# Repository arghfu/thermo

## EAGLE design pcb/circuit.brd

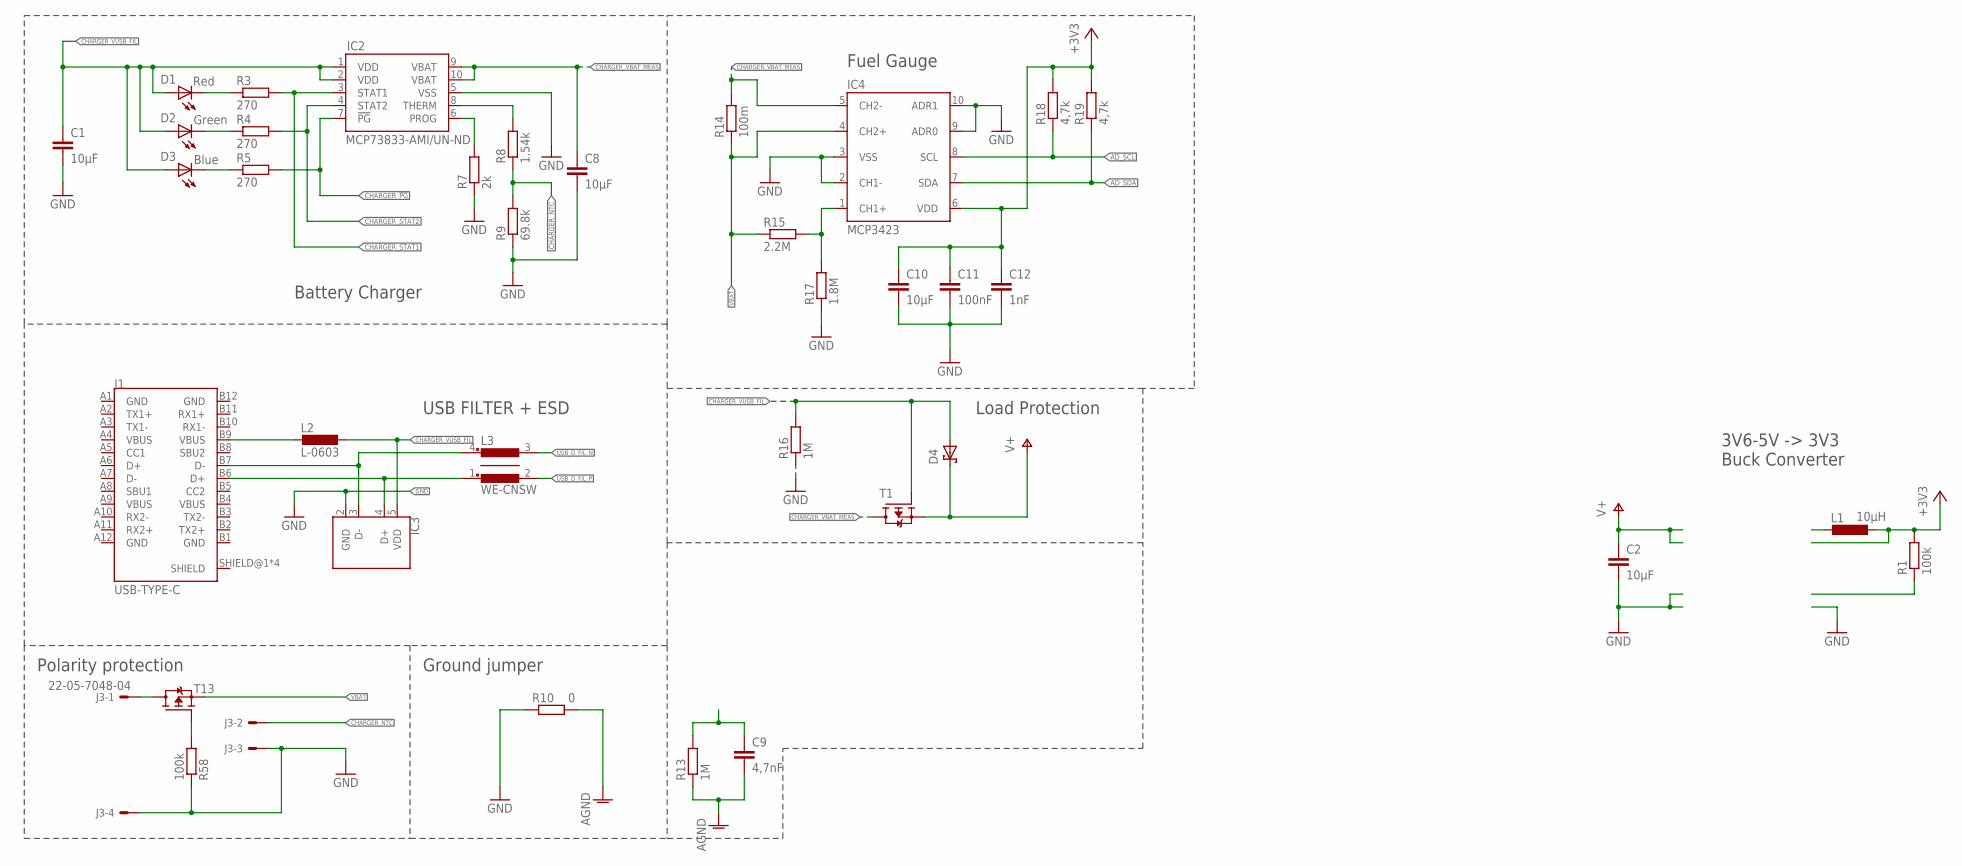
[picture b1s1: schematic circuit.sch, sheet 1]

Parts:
C1, C2, C8, C10: 10µF; C0805
C9: 4,7nF; C0603
C11: 100nF; C0603
C12: 1nF; C0603
D1: Red; LED_2012
D2: Green; LED_2012
D3: Blue; LED_2012
D4: BAT60AE6327HTSA1; SOD323
IC2: MCP73833-AMI/UN-ND; MSOP10
IC3: WE-TVS; SOT23-5L
IC4: MCP3423; MSOP10
J1: USB-TYPE-C; USB-105450-0101
J3: 22-05-7048-04; 7395-04
L1: 10µH; L-1210
L2: L-0603; L0603
L3: WE-CNSW
R1, R58: 100k; R0603
R3, R4, R5: 270; R0603
R7: 2k; R0603
R8: 1.54k; R0603
R9: 69.8k; R0603
R10: 0; R0603
R13, R16: 1M; R0603
R14: 100m; R5025
R15: 2.2M; R0603
R17: 1.8M; R0603
R18, R19: 4,7k; R0603
T1, T13: PMOS; SOT23

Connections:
+3V3: C10.1, C11.1, C12.1, IC4.6 (VDD), L1.1, R1.2, R18.2, R19.2; also elsewhere on the board
AD_CH2+: IC4.1 (CH1+), R15.2, R17.2
AD_SCL: IC4.8 (SCL), R18.1; also elsewhere on the board
AD_SDA: IC4.7 (SDA), R19.1; also elsewhere on the board
AGND: C9.2, R10.2, R13.1; also elsewhere on the board
BUCK_LX: L1.2
CHARGER_!PG!: IC2.7 (!PG), R5.2; also elsewhere on the board
CHARGER_!PG!_LED: D3.1 (C), R5.1
CHARGER_NTC: J3.2, R8.1, R9.2
CHARGER_PROG: IC2.6 (PROG), R7.2
CHARGER_STAT1: IC2.3 (STAT1), R3.2; also elsewhere on the board
CHARGER_STAT1_LED: D1.1 (C), R3.1
CHARGER_STAT2: IC2.4 (STAT2), R4.2; also elsewhere on the board
CHARGER_STAT2_LED: D2.1 (C), R4.1
CHARGER_THERM: IC2.8 (THERM), R8.2
CHARGER_VBAT_MEAS: C8.1, IC2.9 (VBAT), IC2.10 (VBAT), IC4.5 (CH2-), R14.2, T1.3 (D)
CHARGER_VUSB_FIL: C1.1, D1.2 (A), D2.2 (A), D3.2 (A), D4.2 (A), IC2.1 (VDD), IC2.2 (VDD), IC3.5 (VDD), L2.1, R16.2, T1.1 (G); also elsewhere on the board
GND: C1.2, C2.2, C8.2, C10.2, C11.2, C12.2, IC2.5 (VSS), IC3.2 (GND), IC4.2 (CH1-), IC4.3 (VSS), IC4.9 (ADR0), IC4.10 (ADR1), J3.3, J3.4, R7.1, R9.1, R10.1, R16.1, R17.1, R58.1; also elsewhere on the board
unnamed: J1.B9 (VBUS), L2.2
USB_D_FIL_N: L3.3; also elsewhere on the board
USB_D_FIL_P: L3.2; also elsewhere on the board
USB_D_N: IC3.3 (D-), J1.A7 (D-), J1.B7 (D-), L3.4
USB_D_P: IC3.4 (D+), J1.A6 (D+), J1.B6 (D+), L3.1
USB_SHIELD: C9.1, R13.2
V+: C2.1, D4.1 (C), T1.2 (S)
VAT_EN: R58.2, T13.1 (G)
VBAT: IC4.4 (CH2+), R14.1, R15.1, T13.2 (S)
VBAT_UNPROT: J3.1, T13.3 (D)

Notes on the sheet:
3V6-5V -> 3V3 Buck Converter
Fuel Gauge
Battery Charger
Load Protection
USB FILTER + ESD
Polarity protection
Ground jumper

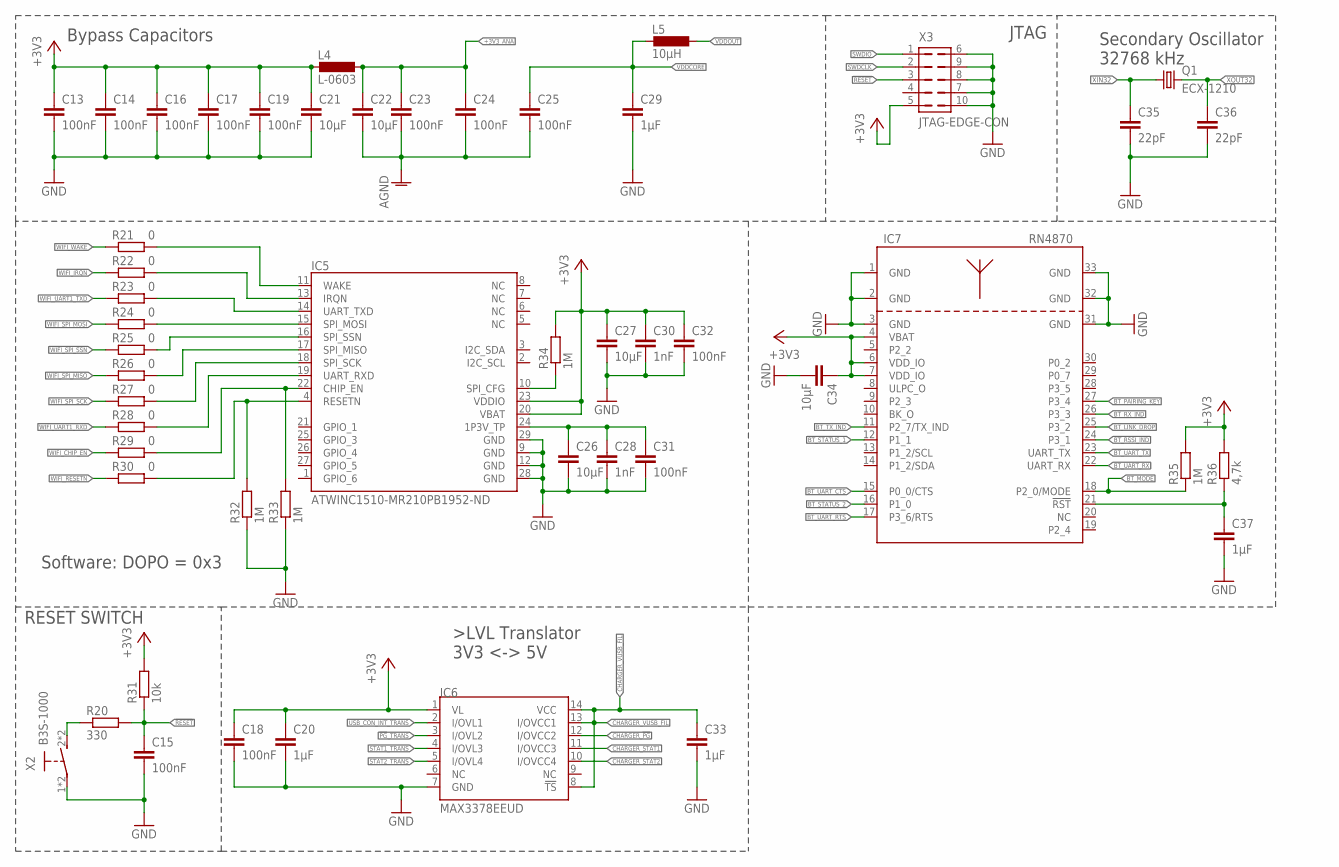
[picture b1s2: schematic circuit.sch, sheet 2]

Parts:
C13, C14, C15, C16, C17, C18, C19, C23, C24, C25, C31, C32: 100nF; C0603
C20, C29, C33, C37: 1µF; C0603
C21, C22, C26, C27, C34: 10µF; C0805
C28, C30: 1nF; C0603
C35, C36: 22pF; C0603
IC5: ATWINC1510-MR210PB1952-ND; ATWINC15X0-MODULE
IC6: MAX3378EEUD; TSSOP14
IC7: RN4870; RN4870-MODULE
L4: L-0603; L0603
L5: 10µH; L-1210
Q1: ECX-1210
R20: 330; R0603
R21, R22, R23, R24, R25, R26, R27, R28, R29, R30: 0; R0603
R31: 10k; R0603
R32, R33, R34, R35: 1M; R0603
R36: 4,7k; R0603
X2: B3S-1000; B3S
X3: JTAG-EDGE-CON; DEBUG-CON

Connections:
!PG!_TRANS: IC6.3 (I/OVL2); also elsewhere on the board
!RESET!: C15.1, R20.2, R31.1, X3.3; also elsewhere on the board
!RESET!_B: R20.1, X2.2 (S), X2.4 (S)
+3V3: C13.1, C14.1, C16.1, C17.1, C18.1, C19.1, C20.1, C21.1, C27.1, C30.1, C32.1, C34.1, IC5.20 (VBAT), IC5.23 (VDDIO), IC6.1 (VL), IC7.4 (VBAT), IC7.6 (VDD_IO), IC7.7 (VDD_IO), L4.2, R31.2, R34.2, R35.2, R36.2, X3.5; also elsewhere on the board
+3V3_ANA: C22.1, C23.1, C24.1, L4.1; also elsewhere on the board
AGND: C22.2, C23.2, C24.2, C25.2; also elsewhere on the board
BT_!RESET!: C37.1, IC7.21 (!RST!), R36.1
BT_LINK_DROP: IC7.25 (P3_2); also elsewhere on the board
BT_MODE: IC7.18 (P2_0/MODE), R35.1; also elsewhere on the board
BT_PAIRING_KEY: IC7.27 (P3_4); also elsewhere on the board
BT_RSSI_IND: IC7.24 (P3_1); also elsewhere on the board
BT_RX_IND: IC7.26 (P3_3); also elsewhere on the board
BT_STATUS_1: IC7.12 (P1_1); also elsewhere on the board
BT_STATUS_2: IC7.16 (P1_0); also elsewhere on the board
BT_TX_IND: IC7.11 (P2_7/TX_IND); also elsewhere on the board
BT_UART_CTS: IC7.15 (P0_0/CTS); also elsewhere on the board
BT_UART_RTS: IC7.17 (P3_6/RTS); also elsewhere on the board
BT_UART_RX: IC7.22 (UART_RX); also elsewhere on the board
BT_UART_TX: IC7.23 (UART_TX); also elsewhere on the board
CHARGER_!PG!: IC6.12 (I/OVCC2); also elsewhere on the board
CHARGER_STAT1: IC6.11 (I/OVCC3); also elsewhere on the board
CHARGER_STAT2: IC6.10 (I/OVCC4); also elsewhere on the board
CHARGER_VUSB_FIL: C33.1, IC6.8 (!TS!), IC6.13 (I/OVCC1), IC6.14 (VCC); also elsewhere on the board
GND: C13.2, C14.2, C15.2, C16.2, C17.2, C18.2, C19.2, C20.2, C21.2, C26.2, C27.2, C28.2, C29.2, C30.2, C31.2, C32.2, C33.2, C34.2, C35.2, C36.2, C37.2, IC5.9 (GND), IC5.12 (GND), IC5.28 (GND), IC5.29 (GND), IC6.7 (GND), IC7.1 (GND), IC7.2 (GND), IC7.3 (GND), IC7.31 (GND), IC7.32 (GND), IC7.33 (GND), R32.1, R33.1, X2.1, X2.3, X3.6, X3.7, X3.8, X3.9, X3.10; also elsewhere on the board
STAT1_TRANS: IC6.4 (I/OVL3); also elsewhere on the board
STAT2_TRANS: IC6.5 (I/OVL4); also elsewhere on the board
SWDCLK: X3.2; also elsewhere on the board
SWDIO: X3.1; also elsewhere on the board
USB_CON_INT_TRANS: IC6.2 (I/OVL1); also elsewhere on the board
VDDCORE: C25.1, C29.1, L5.2; also elsewhere on the board
VDDOUT: L5.1; also elsewhere on the board
WIFI_1P3V_TP: C26.1, C28.1, C31.1, IC5.24 (1P3V_TP)
WIFI_CHIP_EN: R29.1; also elsewhere on the board
WIFI_CHIP_EN_D: IC5.22 (CHIP_EN), R29.2, R33.2
WIFI_IRQN: R22.1; also elsewhere on the board
WIFI_IRQN_D: IC5.13 (IRQN), R22.2
WIFI_MOSI_D: IC5.15 (SPI_MOSI), R24.2
WIFI_RESETN: R30.1; also elsewhere on the board
WIFI_RESETN_D: IC5.4 (RESETN), R30.2, R32.2
WIFI_SPI_CFG: IC5.10 (SPI_CFG), R34.1
WIFI_SPI_MISO: R26.1; also elsewhere on the board
WIFI_SPI_MISO_D: IC5.17 (SPI_MISO), R26.2
WIFI_SPI_MOSI: R24.1; also elsewhere on the board
WIFI_SPI_SCK: R27.1; also elsewhere on the board
WIFI_SPI_SCK_D: IC5.18 (SPI_SCK), R27.2
WIFI_SPI_SSN: R25.1; also elsewhere on the board
WIFI_SPI_SSN_D: IC5.16 (SPI_SSN), R25.2
WIFI_UART1_RXD: R28.1; also elsewhere on the board
WIFI_UART1_RXD_D: IC5.19 (UART_RXD), R28.2
WIFI_UART1_TXD: R23.1; also elsewhere on the board
WIFI_UART_TXD_D: IC5.14 (UART_TXD), R23.2
WIFI_WAKE: R21.1; also elsewhere on the board
WIFI_WAKE_D: IC5.11 (WAKE), R21.2
XIN32: C35.1, Q1.1; also elsewhere on the board
XOUT32: C36.1, Q1.2; also elsewhere on the board

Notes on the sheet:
Bypass Capacitors
Secondary Oscillator 32768 kHz
RESET SWITCH
JTAG
Software: DOPO = 0x3

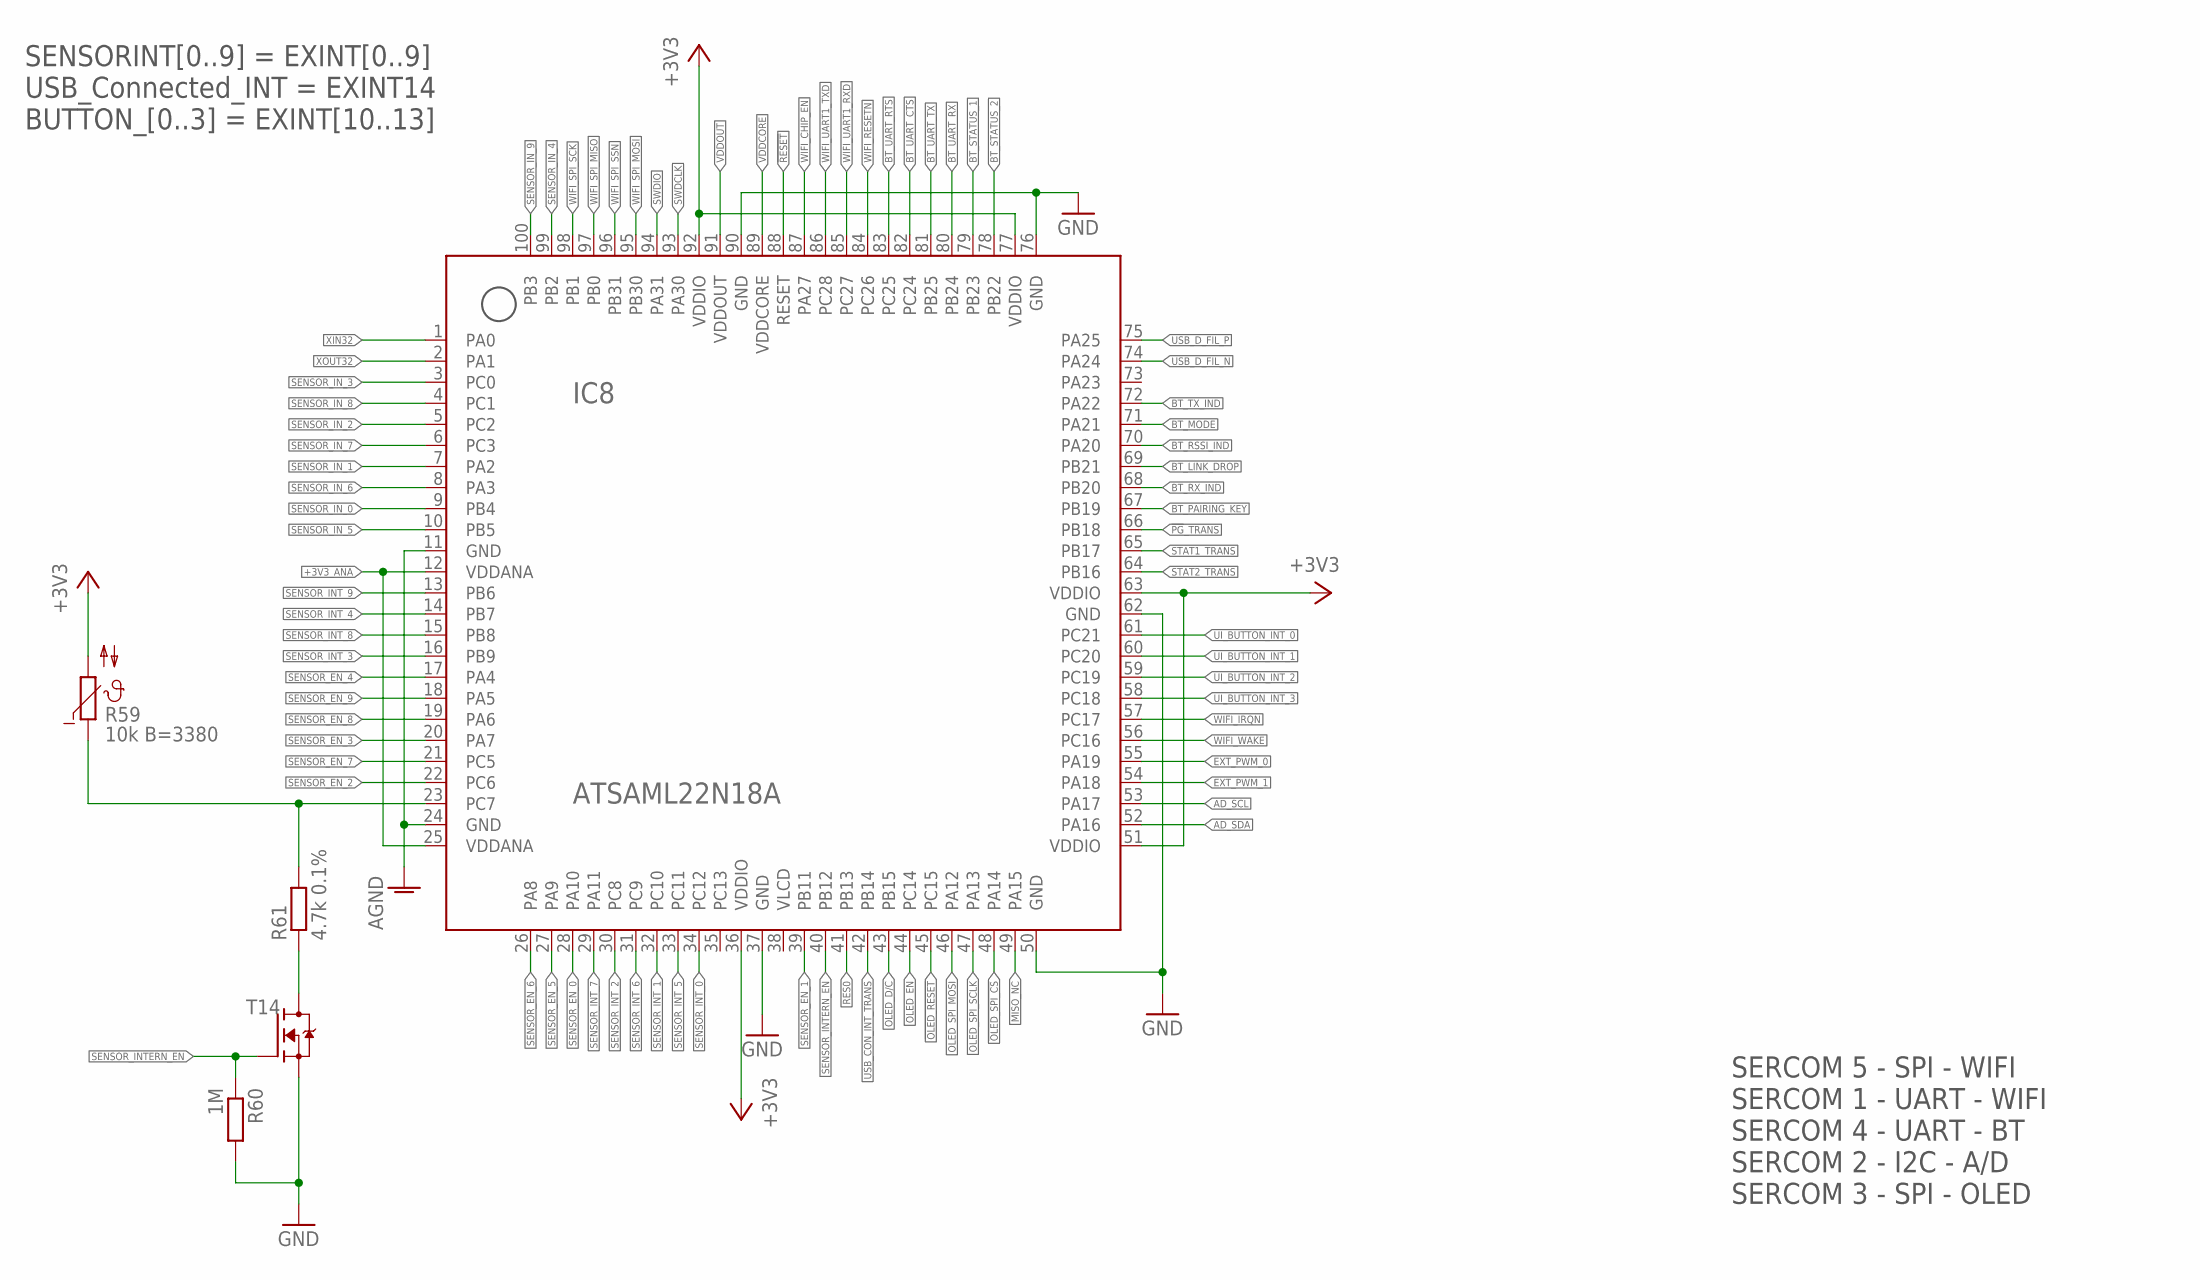
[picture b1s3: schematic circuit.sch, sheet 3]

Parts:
IC8: ATSAML22N18A; TQFP100
R59: 10k B=3380; R0603
R60: 1M; R0603
R61: 4.7k 0.1%; R0603
T14: NMOSSOT323; SOT-323

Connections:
!OLED_RESET: IC8.45 (PC15); also elsewhere on the board
!OLED_SPI_CS: IC8.48 (PA14); also elsewhere on the board
!PG!_TRANS: IC8.66 (PB18); also elsewhere on the board
!RESET!: IC8.88 (RESET); also elsewhere on the board
+3V3: IC8.36 (VDDIO), IC8.51 (VDDIO), IC8.63 (VDDIO), IC8.77 (VDDIO), IC8.92 (VDDIO), R59.2; also elsewhere on the board
+3V3_ANA: IC8.12 (VDDANA), IC8.25 (VDDANA); also elsewhere on the board
AD_SCL: IC8.53 (PA17); also elsewhere on the board
AD_SDA: IC8.52 (PA16); also elsewhere on the board
AGND: IC8.11 (GND), IC8.24 (GND); also elsewhere on the board
BT_LINK_DROP: IC8.69 (PB21); also elsewhere on the board
BT_MODE: IC8.71 (PA21); also elsewhere on the board
BT_PAIRING_KEY: IC8.67 (PB19); also elsewhere on the board
BT_RSSI_IND: IC8.70 (PA20); also elsewhere on the board
BT_RX_IND: IC8.68 (PB20); also elsewhere on the board
BT_STATUS_1: IC8.79 (PB23); also elsewhere on the board
BT_STATUS_2: IC8.78 (PB22); also elsewhere on the board
BT_TX_IND: IC8.72 (PA22); also elsewhere on the board
BT_UART_CTS: IC8.82 (PC24); also elsewhere on the board
BT_UART_RTS: IC8.83 (PC25); also elsewhere on the board
BT_UART_RX: IC8.80 (PB24); also elsewhere on the board
BT_UART_TX: IC8.81 (PB25); also elsewhere on the board
EXT_PWM_0: IC8.55 (PA19); also elsewhere on the board
EXT_PWM_1: IC8.54 (PA18); also elsewhere on the board
GND: IC8.37 (GND), IC8.50 (GND), IC8.62 (GND), IC8.76 (GND), IC8.90 (GND), R60.2, T14.2 (S); also elsewhere on the board
MISO_NC: IC8.49 (PA15)
OLED_D/C: IC8.43 (PB15); also elsewhere on the board
OLED_EN: IC8.44 (PC14); also elsewhere on the board
OLED_SPI_MOSI: IC8.46 (PA12); also elsewhere on the board
OLED_SPI_SCLK: IC8.47 (PA13); also elsewhere on the board
RES0: IC8.41 (PB13); also elsewhere on the board
SENSOR_EN_0: IC8.28 (PA10); also elsewhere on the board
SENSOR_EN_1: IC8.39 (PB11); also elsewhere on the board
SENSOR_EN_2: IC8.22 (PC6); also elsewhere on the board
SENSOR_EN_3: IC8.20 (PA7); also elsewhere on the board
SENSOR_EN_4: IC8.17 (PA4); also elsewhere on the board
SENSOR_EN_5: IC8.27 (PA9); also elsewhere on the board
SENSOR_EN_6: IC8.26 (PA8); also elsewhere on the board
SENSOR_EN_7: IC8.21 (PC5); also elsewhere on the board
SENSOR_EN_8: IC8.19 (PA6); also elsewhere on the board
SENSOR_EN_9: IC8.18 (PA5); also elsewhere on the board
SENSOR_INTERN_DRAIN: R61.1, T14.3 (D)
SENSOR_INTERN_EN: IC8.40 (PB12), R60.1, T14.1 (G); also elsewhere on the board
SENSOR_INTERN_IN: IC8.23 (PC7), R59.1, R61.2
SENSOR_INT_0: IC8.34 (PC12); also elsewhere on the board
SENSOR_INT_1: IC8.32 (PC10); also elsewhere on the board
SENSOR_INT_2: IC8.30 (PC8); also elsewhere on the board
SENSOR_INT_3: IC8.16 (PB9); also elsewhere on the board
SENSOR_INT_4: IC8.14 (PB7); also elsewhere on the board
SENSOR_INT_5: IC8.33 (PC11); also elsewhere on the board
SENSOR_INT_6: IC8.31 (PC9); also elsewhere on the board
SENSOR_INT_7: IC8.29 (PA11); also elsewhere on the board
SENSOR_INT_8: IC8.15 (PB8); also elsewhere on the board
SENSOR_INT_9: IC8.13 (PB6); also elsewhere on the board
SENSOR_IN_0: IC8.9 (PB4); also elsewhere on the board
SENSOR_IN_1: IC8.7 (PA2); also elsewhere on the board
SENSOR_IN_2: IC8.5 (PC2); also elsewhere on the board
SENSOR_IN_3: IC8.3 (PC0); also elsewhere on the board
SENSOR_IN_4: IC8.99 (PB2); also elsewhere on the board
SENSOR_IN_5: IC8.10 (PB5); also elsewhere on the board
SENSOR_IN_6: IC8.8 (PA3); also elsewhere on the board
SENSOR_IN_7: IC8.6 (PC3); also elsewhere on the board
SENSOR_IN_8: IC8.4 (PC1); also elsewhere on the board
SENSOR_IN_9: IC8.100 (PB3); also elsewhere on the board
STAT1_TRANS: IC8.65 (PB17); also elsewhere on the board
STAT2_TRANS: IC8.64 (PB16); also elsewhere on the board
SWDCLK: IC8.93 (PA30); also elsewhere on the board
SWDIO: IC8.94 (PA31); also elsewhere on the board
UI_BUTTON_INT_0: IC8.61 (PC21); also elsewhere on the board
UI_BUTTON_INT_1: IC8.60 (PC20); also elsewhere on the board
UI_BUTTON_INT_2: IC8.59 (PC19); also elsewhere on the board
UI_BUTTON_INT_3: IC8.58 (PC18); also elsewhere on the board
USB_CON_INT_TRANS: IC8.42 (PB14); also elsewhere on the board
USB_D_FIL_N: IC8.74 (PA24); also elsewhere on the board
USB_D_FIL_P: IC8.75 (PA25); also elsewhere on the board
VDDCORE: IC8.89 (VDDCORE); also elsewhere on the board
VDDOUT: IC8.91 (VDDOUT); also elsewhere on the board
WIFI_CHIP_EN: IC8.87 (PA27); also elsewhere on the board
WIFI_IRQN: IC8.57 (PC17); also elsewhere on the board
WIFI_RESETN: IC8.84 (PC26); also elsewhere on the board
WIFI_SPI_MISO: IC8.97 (PB0); also elsewhere on the board
WIFI_SPI_MOSI: IC8.95 (PB30); also elsewhere on the board
WIFI_SPI_SCK: IC8.98 (PB1); also elsewhere on the board
WIFI_SPI_SSN: IC8.96 (PB31); also elsewhere on the board
WIFI_UART1_RXD: IC8.85 (PC27); also elsewhere on the board
WIFI_UART1_TXD: IC8.86 (PC28); also elsewhere on the board
WIFI_WAKE: IC8.56 (PC16); also elsewhere on the board
XIN32: IC8.1 (PA0); also elsewhere on the board
XOUT32: IC8.2 (PA1); also elsewhere on the board

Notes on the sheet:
SERCOM 5 - SPI - WIFI SERCOM 1 - UART - WIFI SERCOM 4 - UART - BT SERCOM 2 - I2C - A/D SERCOM 3 - SPI - OLED
SENSORINT[0..9] = EXINT[0..9] USB_Connected_INT = EXINT14 BUTTON_[0..3] = EXINT[10..13]

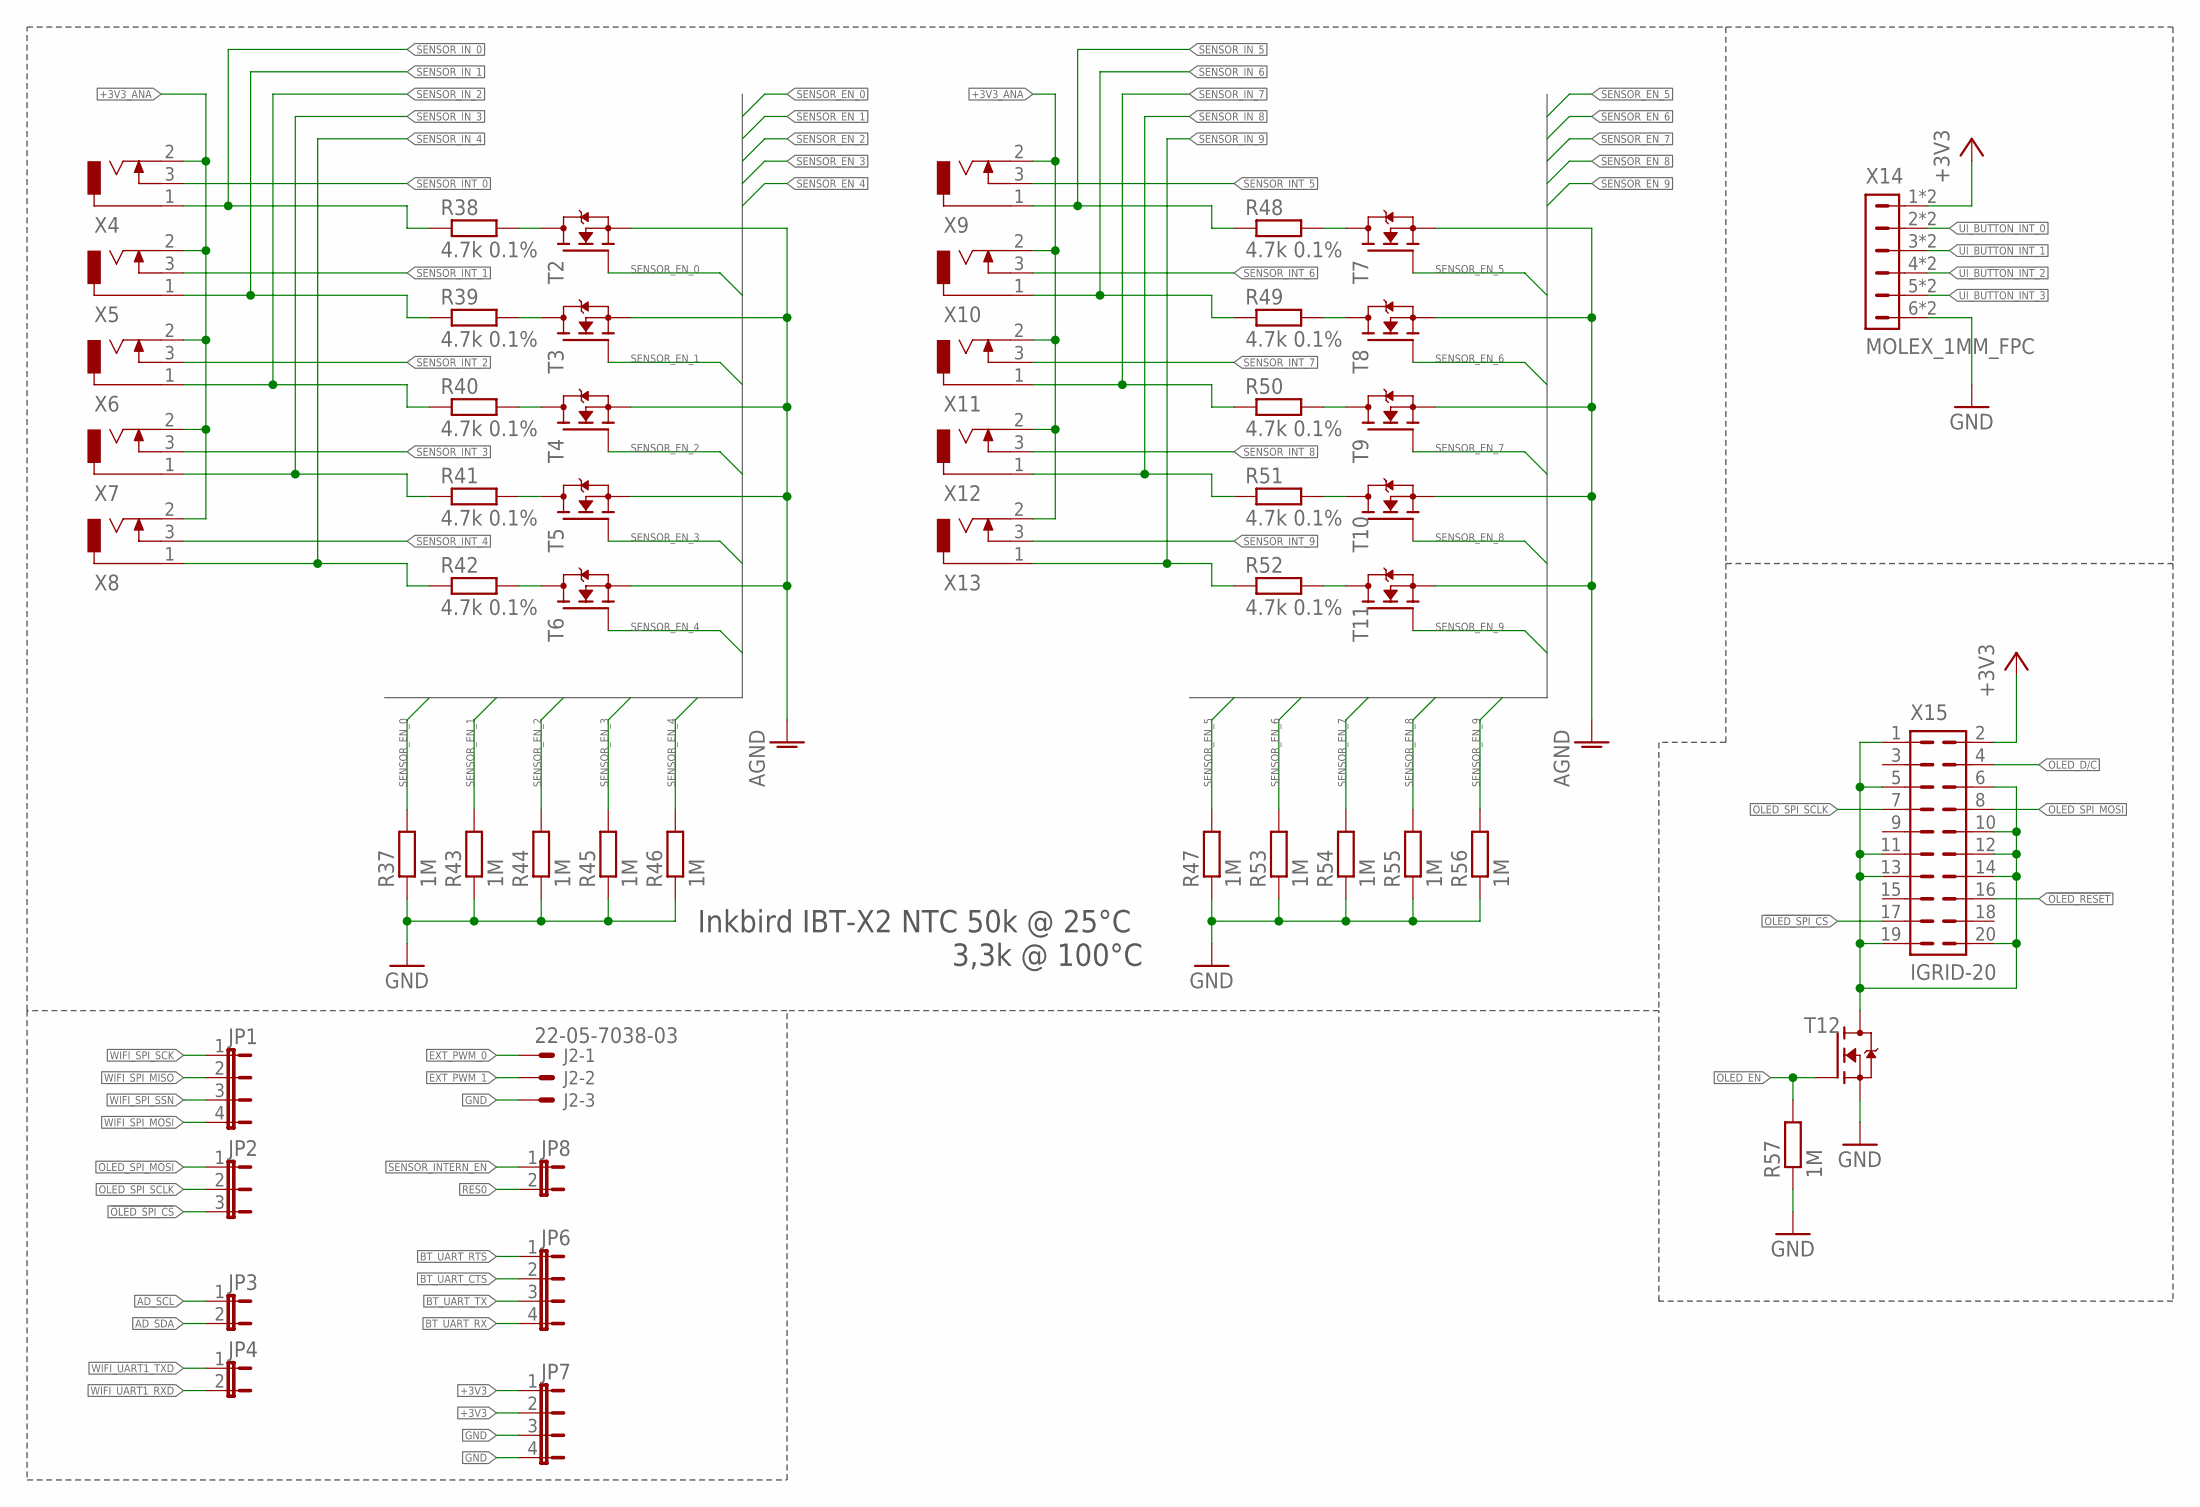
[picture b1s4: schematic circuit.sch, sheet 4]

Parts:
J2: 22-05-7038-03; 7395-03
JP1, JP6, JP7: JP4
JP2: JP3
JP3, JP4, JP8: JP2
R37, R43, R44, R45, R46, R47, R53, R54, R55, R56, R57: 1M; R0603
R38, R39, R40, R41, R42, R48, R49, R50, R51, R52: 4.7k 0.1%; R0603
T2, T3, T4, T5, T6, T7, T8, T9, T10, T11, T12: NMOSSOT323; SOT-323
X4, X5, X6, X7, X8: 2.5MM-AUDIO-JACK-MONODRILL; 2.5MM-AUDIO-JACK-MONO
X9, X10, X11, X12, X13: 2.5MM-AUDIO-JACK-MONONO_DRILL; 2.5MM-AUDIO-JACK-MONO-2
X14: MOLEX_1MM_FPC; 1MM_FPC_ZIF
X15: IGRID-20; I-GRID-20

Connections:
!OLED_RESET: X15.16; also elsewhere on the board
!OLED_SPI_CS: JP2.3, X15.17; also elsewhere on the board
+3V3: JP7.1, JP7.2, X14.1, X14.7 (1), X15.2; also elsewhere on the board
+3V3_ANA: X4.2, X5.2, X6.2, X7.2, X8.2, X9.2, X10.2, X11.2, X12.2, X13.2; also elsewhere on the board
AD_SCL: JP3.1; also elsewhere on the board
AD_SDA: JP3.2; also elsewhere on the board
AGND: T2.2 (S), T3.2 (S), T4.2 (S), T5.2 (S), T6.2 (S), T7.2 (S), T8.2 (S), T9.2 (S), T10.2 (S), T11.2 (S); also elsewhere on the board
BT_UART_CTS: JP6.2; also elsewhere on the board
BT_UART_RTS: JP6.1; also elsewhere on the board
BT_UART_RX: JP6.4; also elsewhere on the board
BT_UART_TX: JP6.3; also elsewhere on the board
EXT_PWM_0: J2.1; also elsewhere on the board
EXT_PWM_1: J2.2; also elsewhere on the board
GND: J2.3, JP7.3, JP7.4, R37.1, R43.1, R44.1, R45.1, R46.1, R47.1, R53.1, R54.1, R55.1, R56.1, R57.1, T12.2 (S), X14.6, X14.12 (6); also elsewhere on the board
OLED_D/C: X15.4; also elsewhere on the board
OLED_EN: R57.2, T12.1 (G); also elsewhere on the board
OLED_EN_DRAIN: T12.3 (D), X15.1, X15.5, X15.6, X15.10, X15.11, X15.12, X15.13, X15.14, X15.19, X15.20
OLED_SPI_MOSI: JP2.1, X15.8; also elsewhere on the board
OLED_SPI_SCLK: JP2.2, X15.7; also elsewhere on the board
RES0: JP8.2; also elsewhere on the board
SENSOR_EN_0: R37.2, T2.1 (G); also elsewhere on the board
SENSOR_EN_1: R43.2, T3.1 (G); also elsewhere on the board
SENSOR_EN_2: R44.2, T4.1 (G); also elsewhere on the board
SENSOR_EN_3: R45.2, T5.1 (G); also elsewhere on the board
SENSOR_EN_4: R46.2, T6.1 (G); also elsewhere on the board
SENSOR_EN_5: R47.2, T7.1 (G); also elsewhere on the board
SENSOR_EN_6: R53.2, T8.1 (G); also elsewhere on the board
SENSOR_EN_7: R54.2, T9.1 (G); also elsewhere on the board
SENSOR_EN_8: R55.2, T10.1 (G); also elsewhere on the board
SENSOR_EN_9: R56.2, T11.1 (G); also elsewhere on the board
SENSOR_INTERN_EN: JP8.1; also elsewhere on the board
SENSOR_INT_0: X4.3; also elsewhere on the board
SENSOR_INT_1: X5.3; also elsewhere on the board
SENSOR_INT_2: X6.3; also elsewhere on the board
SENSOR_INT_3: X7.3; also elsewhere on the board
SENSOR_INT_4: X8.3; also elsewhere on the board
SENSOR_INT_5: X9.3; also elsewhere on the board
SENSOR_INT_6: X10.3; also elsewhere on the board
SENSOR_INT_7: X11.3; also elsewhere on the board
SENSOR_INT_8: X12.3; also elsewhere on the board
SENSOR_INT_9: X13.3; also elsewhere on the board
SENSOR_IN_0: R38.1, X4.1; also elsewhere on the board
SENSOR_IN_0_DRAIN: R38.2, T2.3 (D)
SENSOR_IN_1: R39.1, X5.1; also elsewhere on the board
SENSOR_IN_1_DRAIN: R39.2, T3.3 (D)
SENSOR_IN_2: R40.1, X6.1; also elsewhere on the board
SENSOR_IN_2_DRAIN: R40.2, T4.3 (D)
SENSOR_IN_3: R41.1, X7.1; also elsewhere on the board
SENSOR_IN_3_DRAIN: R41.2, T5.3 (D)
SENSOR_IN_4: R42.1, X8.1; also elsewhere on the board
SENSOR_IN_4_DRAIN: R42.2, T6.3 (D)
SENSOR_IN_5: R48.1, X9.1; also elsewhere on the board
SENSOR_IN_5_DRAIN: R48.2, T7.3 (D)
SENSOR_IN_6: R49.1, X10.1; also elsewhere on the board
SENSOR_IN_6_DRAIN: R49.2, T8.3 (D)
SENSOR_IN_7: R50.1, X11.1; also elsewhere on the board
SENSOR_IN_7_DRAIN: R50.2, T9.3 (D)
SENSOR_IN_8: R51.1, X12.1; also elsewhere on the board
SENSOR_IN_8_DRAIN: R51.2, T10.3 (D)
SENSOR_IN_9: R52.1, X13.1; also elsewhere on the board
SENSOR_IN_9_DRAIN: R52.2, T11.3 (D)
UI_BUTTON_INT_0: X14.2, X14.8 (2); also elsewhere on the board
UI_BUTTON_INT_1: X14.3, X14.9 (3); also elsewhere on the board
UI_BUTTON_INT_2: X14.4, X14.10 (4); also elsewhere on the board
UI_BUTTON_INT_3: X14.5, X14.11 (5); also elsewhere on the board
WIFI_SPI_MISO: JP1.2; also elsewhere on the board
WIFI_SPI_MOSI: JP1.4; also elsewhere on the board
WIFI_SPI_SCK: JP1.1; also elsewhere on the board
WIFI_SPI_SSN: JP1.3; also elsewhere on the board
WIFI_UART1_RXD: JP4.2; also elsewhere on the board
WIFI_UART1_TXD: JP4.1; also elsewhere on the board

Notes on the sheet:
Inkbird IBT-X2 NTC 50k @ 25°C 3,3k @ 100°C

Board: 2 copper layers, 144 parts (0 on the bottom side), 132 nets, no tracks yet.

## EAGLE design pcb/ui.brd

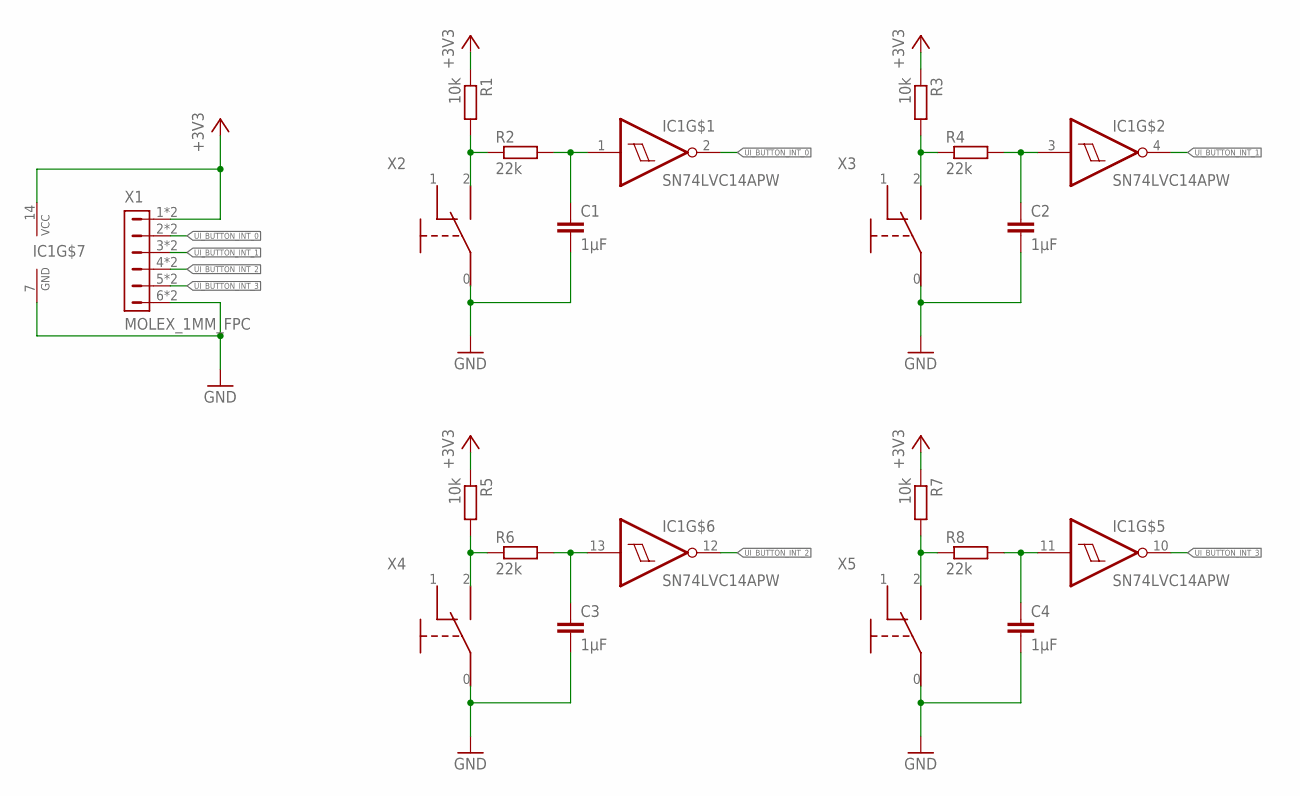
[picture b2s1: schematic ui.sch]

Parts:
C1, C2, C3, C4: 1µF; C0805
IC1: SN74LVC14APW; TSSOP14
R1, R3, R5, R7: 10k; R0805
R2, R4, R6, R8: 22k; R0805
X1: MOLEX_1MM_FPC; 1MM_FPC_ZIF
X2, X3, X4, X5: PVA2OAH11.7NV2; BUTTON-2

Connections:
+3V3: IC1.14 (VCC), R1.1, R3.1, R5.1, R7.1, X1.1, X1.7 (1)
GND: C1.2, C2.2, C3.2, C4.2, IC1.7 (GND), X1.6, X1.12 (6), X2.0, X3.0, X4.0, X5.0
unnamed: R1.2, R2.1, X2.2
unnamed: C1.1, IC1.1 (I), R2.2
unnamed: R3.2, R4.1, X3.2
unnamed: C2.1, IC1.3 (I), R4.2
unnamed: R5.2, R6.1, X4.2
unnamed: C3.1, IC1.13 (I), R6.2
unnamed: R7.2, R8.1, X5.2
unnamed: C4.1, IC1.11 (I), R8.2
UI_BUTTON_INT_0: IC1.2 (O), X1.2, X1.8 (2)
UI_BUTTON_INT_1: IC1.4 (O), X1.3, X1.9 (3)
UI_BUTTON_INT_2: IC1.12 (O), X1.4, X1.10 (4)
UI_BUTTON_INT_3: IC1.10 (O), X1.5, X1.11 (5)

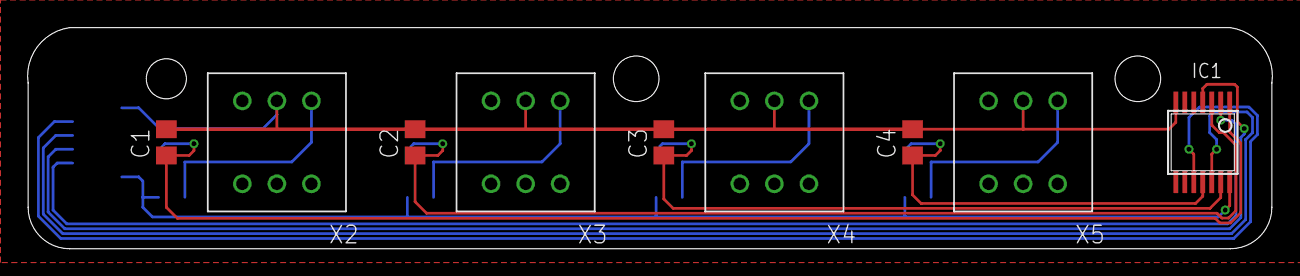
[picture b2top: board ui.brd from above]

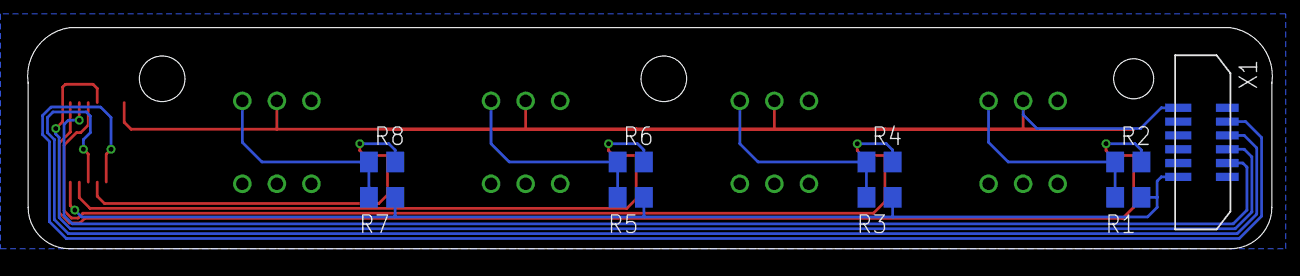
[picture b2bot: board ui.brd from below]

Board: 2 copper layers, 90.1 x 16.0 mm, 18 parts (9 on the bottom side), 14 nets.

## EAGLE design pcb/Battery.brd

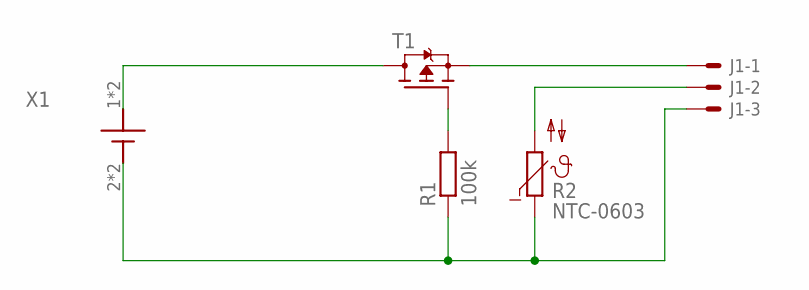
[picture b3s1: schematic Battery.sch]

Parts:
J1: 22-05-7038-03; 7395-03
R1: 100k; R0603
R2: NTC-0603; R0603
T1: PMOS; SOT23
X1: LI-ION_BATHOL2; HOLDER_2

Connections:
BAT: J1.1, T1.2 (S)
GND: J1.3, R1.1, R2.1, X1.2 (VBAT-1), X1.3 (VBAT-1)
unnamed: T1.3 (D), X1.1 (VBAT+1), X1.4 (VBAT+1)
unnamed: R1.2, T1.1 (G)
NTC: J1.2, R2.2

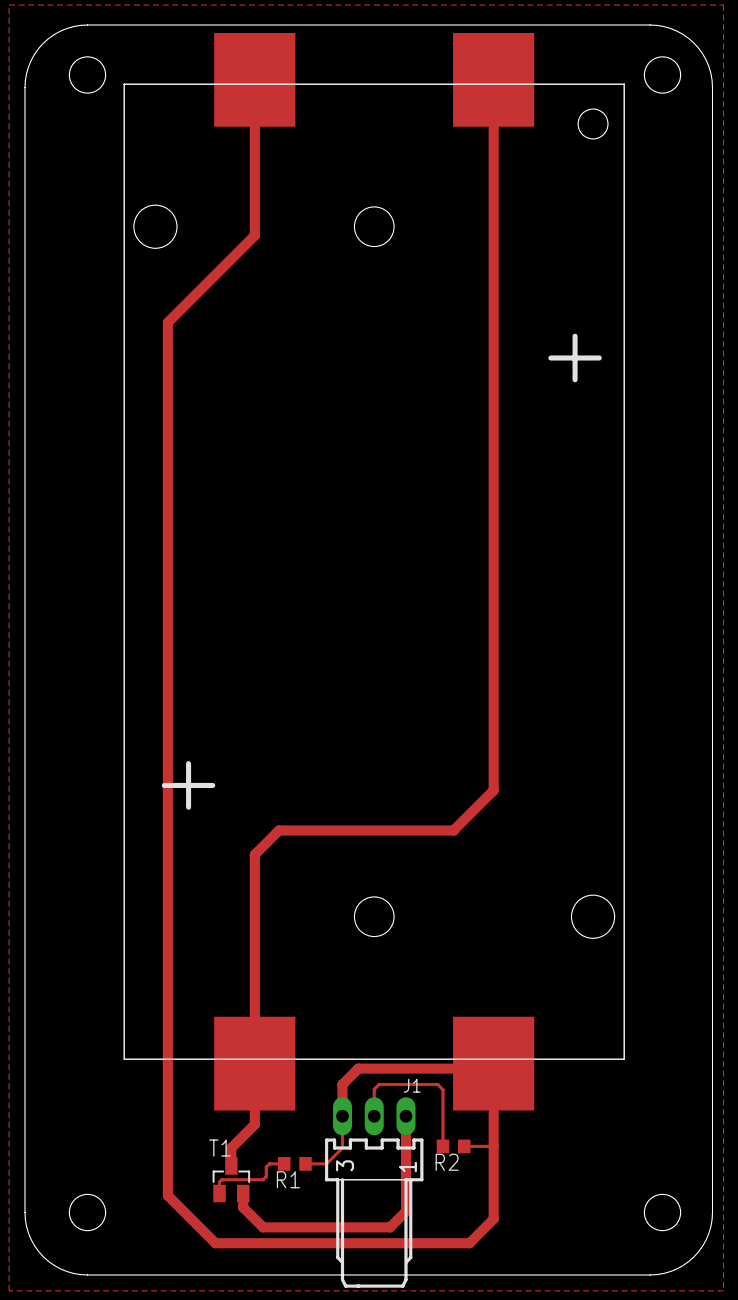
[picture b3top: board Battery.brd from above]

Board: 2 copper layers, 55.0 x 100.0 mm, 5 parts (0 on the bottom side), 5 nets.

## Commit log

2017-11-26 Initial PCB commit
2017-11-26 Schematic: - OLED added Datasheets: - SAML22 AppNotes added
2017-12-01 Schematic
    -added part numbers
    -all devices are connected
2017-12-07 Board dimension created
    -reworked schematics
    -added PCB for battery-holder
    -added PCB for UI
2017-12-07 Routing
    -routing 2.5mm Sensor Connectors started
2017-12-10 Power Unit
    - placed power devices
2017-12-12 AD Converter placed
2017-12-14 Power Unit Refactored
2017-12-18 Power Unit
    -power unit routed
2017-12-18 Senor Pinout refactored
2017-12-20 routed sensor 0,1,5,6
2017-12-23 routed RN4970
2017-12-24 started routing ATWINC
2017-12-25 finished routing ATwinc
2017-12-25 routing finished
2017-12-25 polygons added
2017-12-26 refactoring
2017-12-27 Added Internal NTC
2017-12-27 Added Debug-Pin names
2017-12-27 Gerber Files
    added Gerber files for elecrow.com
2017-12-29 refactored
2017-12-29 updated 3d Models
2017-12-29 LED Footprint changed
2017-12-29 new gerber files
2018-04-24 reworked some ground routes
2018-11-11 Datasheets removed
2019-03-21 datasheets and app. notes
